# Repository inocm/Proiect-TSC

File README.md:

# Proiect InkTime: Smartwatch nRF52840

## 1. Diagrama Bloc

Diagrama de mai jos ilustreaza interconexiunile dintre unitatea centrala (MCU) si perifericele sistemului.

## 2. Descriere Hardware

Ceasul este construit in jurul lui **nRF52840**, ales pentru eficienta energetica ridicata si radio Bluetooth integrat. Principiul fundamental al proiectului: curentul este consumat exclusiv atunci cand este strict necesar.

### 2.1. Unitatea Centrala (MCU)
* **nRF52840:** Microcontroller cu suport nativ pentru Bluetooth 5.0 si USB. Dispune de doua cristale de cuart pentru precizie maxima in masurarea timpului — unul de 32 MHz (HFXO) pentru operatiunile de baza si radio, si unul de 32.768 kHz (LFXO) pentru RTC si modurile de sleep.
* **Antena:** Semnalul radio este directionat catre o antena ceramica **2450AT18B100E** de 2.4 GHz. Pentru a maximiza performanta RF, planul de cupru de sub antena a fost decupat (zona de „keep-out").

### 2.2. Alimentare si Baterie
* **Incarcator (BQ25180YBGR):** Gestioneaza incarcarea bateriei LiPo printr-o conexiune USB-C, inclusiv controlul power path-ului. Comunicarea se face prin **I2C**, permitand monitorizarea starii de incarcare.
* **Fuel Gauge (MAX17048G+T10):** Monitorizeaza cu precizie nivelul de incarcare al bateriei, cu o eroare sub 1%. Poate notifica MCU-ul printr-un pin de alerta atunci cand tensiunea coboara sub un prag configurat.
* **Regulator (RT6160AWSC):** Convertor buck-boost care livreaza un rail stabil de **3.3V** intregului sistem, indiferent de variatiile tensiunii bateriei.
* **Protectie ESD (USBLC6-2SC6Y):** Amplasata direct langa mufa USB-C, atenueaza descarcarile electrostatice pentru a proteja liniile de date ale interfetei.

### 2.3. Display si Feedback Haptic
* **Display E-Paper:** Avantajul principal al acestei tehnologii este ca nu consuma curent decat in momentul actualizarii imaginii. In stare statica, consumul este practic zero.
* **Circuit de driver E-Paper:** Display-ul necesita tensiuni ridicate pentru a misca cerneala electronica. Un circuit dedicat (bobina, diode Schottky si condensatori de 50V) genereaza tensiunile VGH si VGL necesare. Un P-FET (**SI2301CDS**) comanda complet alimentarea display-ului in standby.
* **Driver Haptic (DRV2605LDGSR):** Controleaza motorul ERM (LCM1027B3605F) cu o biblioteca interna de efecte de vibratie, oferind un feedback mai fin si mai variat fata de o simpla comutare cu tranzistor.

### 2.4. Senzori si Butoane
* **Accelerometru (BMA421):** Utilizat pentru numararea pasilor si detectarea miscarii. Conectat pe magistrala **I2C**, pinii sai de intrerupere (INT1, INT2) pot trezi MCU-ul din sleep la ridicarea incheieturii mainii.
* **Butoane (x3 EVP-AKE31A):** Trei butoane tactile SMD pentru navigarea interfetei (sus, jos, enter). Fiecare buton este echipat cu filtre hardware RC pentru eliminarea problemelor de debounce.

## 3. Asociere Pini nRF52840

| Grupa de pini | Pini folositi | Componenta | Justificarea alegerii / Functia |
| :--- | :--- | :--- | :--- |
| **I2C (SDA/SCL)** | **P0.06 / P0.07** | BQ25180, MAX17048, BMA421, DRV2605 | Magistrala I2C comuna; pozitionati departe de zona antenei pentru a evita interferentele RF. Pull-up 10k pe fiecare linie. |
| **Display (SPI)** | **P0.02 (SCK), P0.03 (MOSI)** | Conector FPC E-Paper | Rutare scurta si directa catre conectorul FPC, minimizand lungimea traseelor de mare viteza. |
| **Display Control** | **P0.05 (CS), P0.15, P0.16, P0.17** | Conector FPC E-Paper | Semnale GPIO pentru DC, Reset, Busy. Pinul Busy actioneaza ca intrerupere hardware. |
| **Power Gate Display** | **P1.01** | P-FET SI2301CDS | Comanda tranzistorul de putere care opreste complet alimentarea display-ului in modul standby. |
| **Butoane** | **P0.13, P0.14 / P1.02** | SW1, SW2, SW3 | Buton Enter, Buton Sus (Port 0) si Buton Jos (Port 1). |
| **Alerte & Intreruperi** | **P1.00 – P1.08** | IMU (INT1/INT2), Alerta baterie | Utilizarea portului P1 pentru semnale lente si intreruperi, izolandu-le de magistralele de date rapide. Permite wake-up eficient. |
| **Haptic Enable** | **P0.12** | DRV2605LDGSR | Pin GPIO pentru pornirea/oprirea cipului haptic. |
| **Fuel Gauge Alert** | **P0.10** | MAX17048 | Notificare de la fuel gauge cand tensiunea bateriei scade sub pragul configurat. |
| **Charger Alert** | **P0.11** | BQ25180 | Semnal de alerta de la incarcator pentru potentiale probleme de alimentare. |
| **USB** | **VBUS, D+, D-** | Conector USB-C KH-TYPE-C-16P | Pini hardware dedicati ai PHY-ului intern nRF52840 pentru comunicatie USB nativa. CC1/CC2 cu pull-down 5.1k. |
| **Programare (SWD)** | **SWDIO, SWDCLK, SWO** | Conector Tag-Connect TC2030 | Pini dedicati din fabrica pentru interfata Serial Wire Debug si programare. |
| **Oscilator HF** | **XC1, XC2** | Cristal 32 MHz (2016) | Pini hardware dedicati (HFXO) pentru cristalul extern necesar functionarii MCU si a modulului radio. |
| **Oscilator LF** | **XL1, XL2** | Cristal 32.768 kHz (3215) | Pini hardware dedicati (LFXO) pentru RTC si functiile de Low-Power Sleep. |

## 4. BOM

### Componente Active

| Qty | Componenta | Designator | Cod JLCPCB | Datasheet |
| :--- | :--- | :--- | :--- | :--- |
| 1 | **nRF52840-QIAA-R** (MCU) | U1 | [C190794](https://jlcpcb.com/partdetail/Nordic_Semicon-NRF52840_QIAA_R/C190794) | [Datasheet](https://infocenter.nordicsemi.com/pdf/nRF52840_PS_v1.8.pdf) |
| 1 | **BQ25180YBGR** (Charger) | IC1 | [C3682423](https://jlcpcb.com/partdetail/TexasInstruments-BQ25180YBGR/C3682423) | [Datasheet](https://www.ti.com/lit/ds/symlink/bq25180.pdf) |
| 1 | **RT6160AWSC** (DC/DC) | IC9 | [C7065276](https://jlcpcb.com/partdetail/Richtek_Tech-RT6160AWSC/C7065276) | [Datasheet](https://www.richtek.com/assets/product_file/RT6160A/DS6160A-05.pdf) |
| 1 | **MAX17048G+T10** (Fuel Gauge) | U3 | [C2682616](https://jlcpcb.com/partdetail/AnalogDevices-MAX17048G_T10/C2682616) | [Datasheet](https://www.analog.com/media/en/technical-documentation/data-sheets/MAX17048-MAX17049.pdf) |
| 1 | **BMA421** (Accelerometru) | IC3 | [C5242966](https://jlcpcb.com/partdetail/Bosch_Sensortec-BMA421/C5242966) | [Datasheet](https://www.bosch-sensortec.com/media/boschsensortec/downloads/datasheets/bst-bma421-ds004.pdf) |
| 1 | **DRV2605LDGSR** (Haptic) | IC4 | [C527464](https://jlcpcb.com/partdetail/TexasInstruments-DRV2605LDGSR/C527464) | [Datasheet](https://www.ti.com/lit/ds/symlink/drv2605l.pdf) |
| 1 | **SI2301CDS** (P-FET) | Q1 | [C10487](https://jlcpcb.com/partdetail/Changjiang_Electronics_Tech_CJ-SI2301CDS/C10487) | [Datasheet](https://www.vishay.com/docs/68749/si2301cds.pdf) |
| 1 | **USBLC6-2SC6Y** (ESD) | D3 | [C7519](https://jlcpcb.com/partdetail/Stmicroelectronics-USBLC6_2SC6Y/C7519) | [Datasheet](https://www.st.com/resource/en/datasheet/usblc6-2.pdf) |

### Conectori & Componente Electromecanice

| Qty | Componenta | Designator | Cod JLCPCB | Datasheet |
| :--- | :--- | :--- | :--- | :--- |
| 1 | **Molex 503480-2400** (FPC 24-pin) | J1 | [C2857160](https://jlcpcb.com/partdetail/Molex-5034802400/C2857160) | [Datasheet](https://www.molex.com/en-us/products/part-detail/5034802400) |
| 1 | **KH-TYPE-C-16P** (USB-C) | J4 | [C2765186](https://jlcpcb.com/partdetail/Kinghelm-KH_TYPE_C_16P/C2765186) | [Datasheet](https://datasheet.lcsc.com/lcsc/2012121836_Kinghelm-KH-TYPE-C-16P_C2765186.pdf) |
| 3 | **EVP-AKE31A** (Butoane) | SW1-SW3 | [C2845028](https://jlcpcb.com/partdetail/Panasonic-EVP_AKE31A/C2845028) | [Datasheet](https://industrial.panasonic.com/cdbs/www-data/pdf/ATV0000/ATV0000CE3.pdf) |
| 1 | **TC2030-IDC** (SWD Header) | J_SWD | — | [Datasheet](https://www.tag-connect.com/product/tc2030-idc) |
| 1 | **2450AT18B100E** (Antena 2.4GHz) | ANT1 | [C5179427](https://jlcpcb.com/partdetail/Johanson_Technology-2450AT18B100E/C5179427) | [Datasheet](https://www.johansontechnology.com/datasheets/2450AT18B100/2450AT18B100.pdf) |

### Componente Pasive (selectie)

| Componenta | Valoare | Pachet | Cantitate | Rol |
| :--- | :--- | :--- | :--- | :--- |
| Condensatori EPD | 1uF / 50V | 0402 | 9 | Driver circuit e-paper (VGH/VGL) |
| Condensatori decuplare | 100nF | 0201 | 5 | Decuplare MCU si periferice |
| Condensatori incarcare cristal | 12pF | 0201 | 4 | Load capacitors 32MHz + 32.768kHz |
| Condensatori bulk MCU | 4.7uF | 0402 | 4 | Stabilizare rail 3V3 MCU |
| Condensatori BQ25180 | 1uF | 0402 | 3 | CIN / CSYS / CBAT charger |
| Condensatori RT6160 | 22uF | 0402 | 2 | Intrare convertor buck-boost |
| Condensator USB | 4.7uF | 0402 | 1 | DECUSB nRF52840 |
| Rezistori I2C pull-up | 10k | 0201 | 2 | Pull-up SDA / SCL |
| Rezistori USB CC | 5.1k | 0201 | 2 | Pull-down CC1 / CC2 USB-C |
| Bobina DC/DC nRF | 10uH | 0402 | 1 | Inductor REG1 intern nRF52840 |
| Bobina RT6160 | 0.47uH | 2012 | 1 | Etaj de putere buck-boost |
| Cristal HF | 32 MHz | 2016 | 1 | HFXO — MCU + radio |
| Cristal LF | 32.768 kHz | 3215 | 1 | LFXO — RTC + sleep |

### Componente Asamblate Manual

| Componenta | Descriere | Datasheet |
| :--- | :--- | :--- |
| Display E-Paper | Panou 1.54" 200×200 px, conectat prin FPC 24-pin | [Datasheet](https://www.tme.eu/Document/0ca57a8ffbcd57b5bca53252eb9d6ec3/WSH-12561.pdf) |
| Baterie LiPo | 3.7V / 250mAh, conectata prin fire la test pad-uri | [Datasheet](https://www.tme.eu/Document/b9e12bf26ad0ba929a22ab5d58f022cd/AKY0106.pdf) |
| Motor ERM | Motor vibratii LCM1027B3605F, lipit direct prin fire | [Datasheet](https://www.mouser.com/pdfDocs/ProductOverview_DFRobot-FIT0774.pdf) |
| Carcasa | Prototip imprimat 3D (FDM / SLS) | [Soon™](https://www.youtube.com/watch?v=xm3YgoEiEDc) |

## 5. Decizii de Design

### 5.1. Amplasarea Componentelor pe PCB

Au fost luate urmatoarele decizii strategice pentru a optimiza spatiul, performanta si integritatea semnalului:

* **PCB pe 4 straturi:** Stackup-ul folosit: Top (semnal), GND plane (layer 2), 3V3 plane (layer 3), Bottom (semnal). Aceasta structura ofera o referinta de masa solida pentru traseele de semnal si reduce EMI-ul intern.

* **Planuri de Masa (GND Pours) pe straturi Top si Bottom:** Poligoanele de GND sunt cusute cu via-uri (stitching vias) si servesc trei scopuri:
    1. **Ecranare EMI:** Reduce cuplajul electromagnetic intre traseele de semnal.
    2. **Disipare Termica:** Ajuta la evacuarea caldurii de la convertorul DC/DC si circuitul de incarcare.
    3. **Referinta RF:** Furnizeaza un plan de masa de calitate pentru performanta optima a antenei Bluetooth.

* **Zona RF Keep-out (Antena):** Antena ceramica de 2.4 GHz este pozitionata la extremitatea placii, cu toate straturile de cupru decupate pe sub ea. Grupul de alimentare (charger, fuel gauge, regulator) este plasat la distanta maxima pentru a evita cuplajul cu traseele RF sensibile.

* **Gruparea Circuitului E-Paper:** Componentele aferente display-ului (bobina, diodele si condensatorii de 50V pentru VGH/VGL) sunt concentrate compact imediat langa conectorul FPC. Traseele de inalta tensiune ramane astfel scurte si departe de liniile sensibile ale MCU.

* **Via-in-pad:** Pentru componentele cu footprint mic (WLCSP, DFN), a fost folosita tehnica via-in-pad. Aceasta genereaza cateva avertismente DRC, dar a fost singura solutie viabila pentru rutarea in spatiul disponibil.

* **Conectorul FPC (Display):** Conectorul flex al display-ului a fost curbat in modelul 3D pentru a se potrivi corect in pozitia de asamblare, folosind comanda bend pentru metal sheets din Fusion 360.

### 5.2. Erori Known si Justificari

#### Erori ERC (Electrical Rule Check)
* **Conflicte de alimentare (U1, U3):** Softul semnaleaza erori deoarece mai multi pini `VDD` se conecteaza la aceeasi retea (`3V3` sau `VBAT`). Conexiunile sunt corecte conform datasheet-urilor; eroarea este un fals pozitiv cauzat de restrictiile prea stricte ale tool-ului in legatura cu tipurile de „Power Source".
* **Pinii de decuplare (DEC1, DEC4):** Similar cu cazul anterior, pinii speciali de decuplare ai nRF52840 sunt conectati corect conform recomandarilor producatorului, insa nu sunt recunoscuti ca noduri clasice de alimentare de catre ERC.
* **Componente fara valoare (SJ1):** Jumper-ul SJ1 este un simplu Solder Jumper pentru configurare hardware — un contact de lipit fara valoare numerica, ceea ce este comportamentul asteptat.
* **"Only one pin on net" (SDA/SCL):** Indica trasee lasate fara conexiune la un capat; nu reprezinta o eroare functionala.

#### Erori DRC (Design Rule Check)
Deoarece acest PCB este un *Proof of Concept* si nu este destinat productiei imediate, unele compromisuri de DRC au fost acceptate constient:
* **Board Outline Clearance (8 erori):** Conectorul USB-C si butoanele sunt apropiate de marginea placii prin constrangeri de form factor, declansand automat aceste avertismente.
* **Polygon Overlap (clearance pad-uri):** Placa foloseste componente minuscule (0201/0402) si este extrem de aglomerata. Planul de masa a fost fortat sa acopere cat mai mult spatiu pentru o disipare termica optima, in detrimentul unui raport DRC perfect.

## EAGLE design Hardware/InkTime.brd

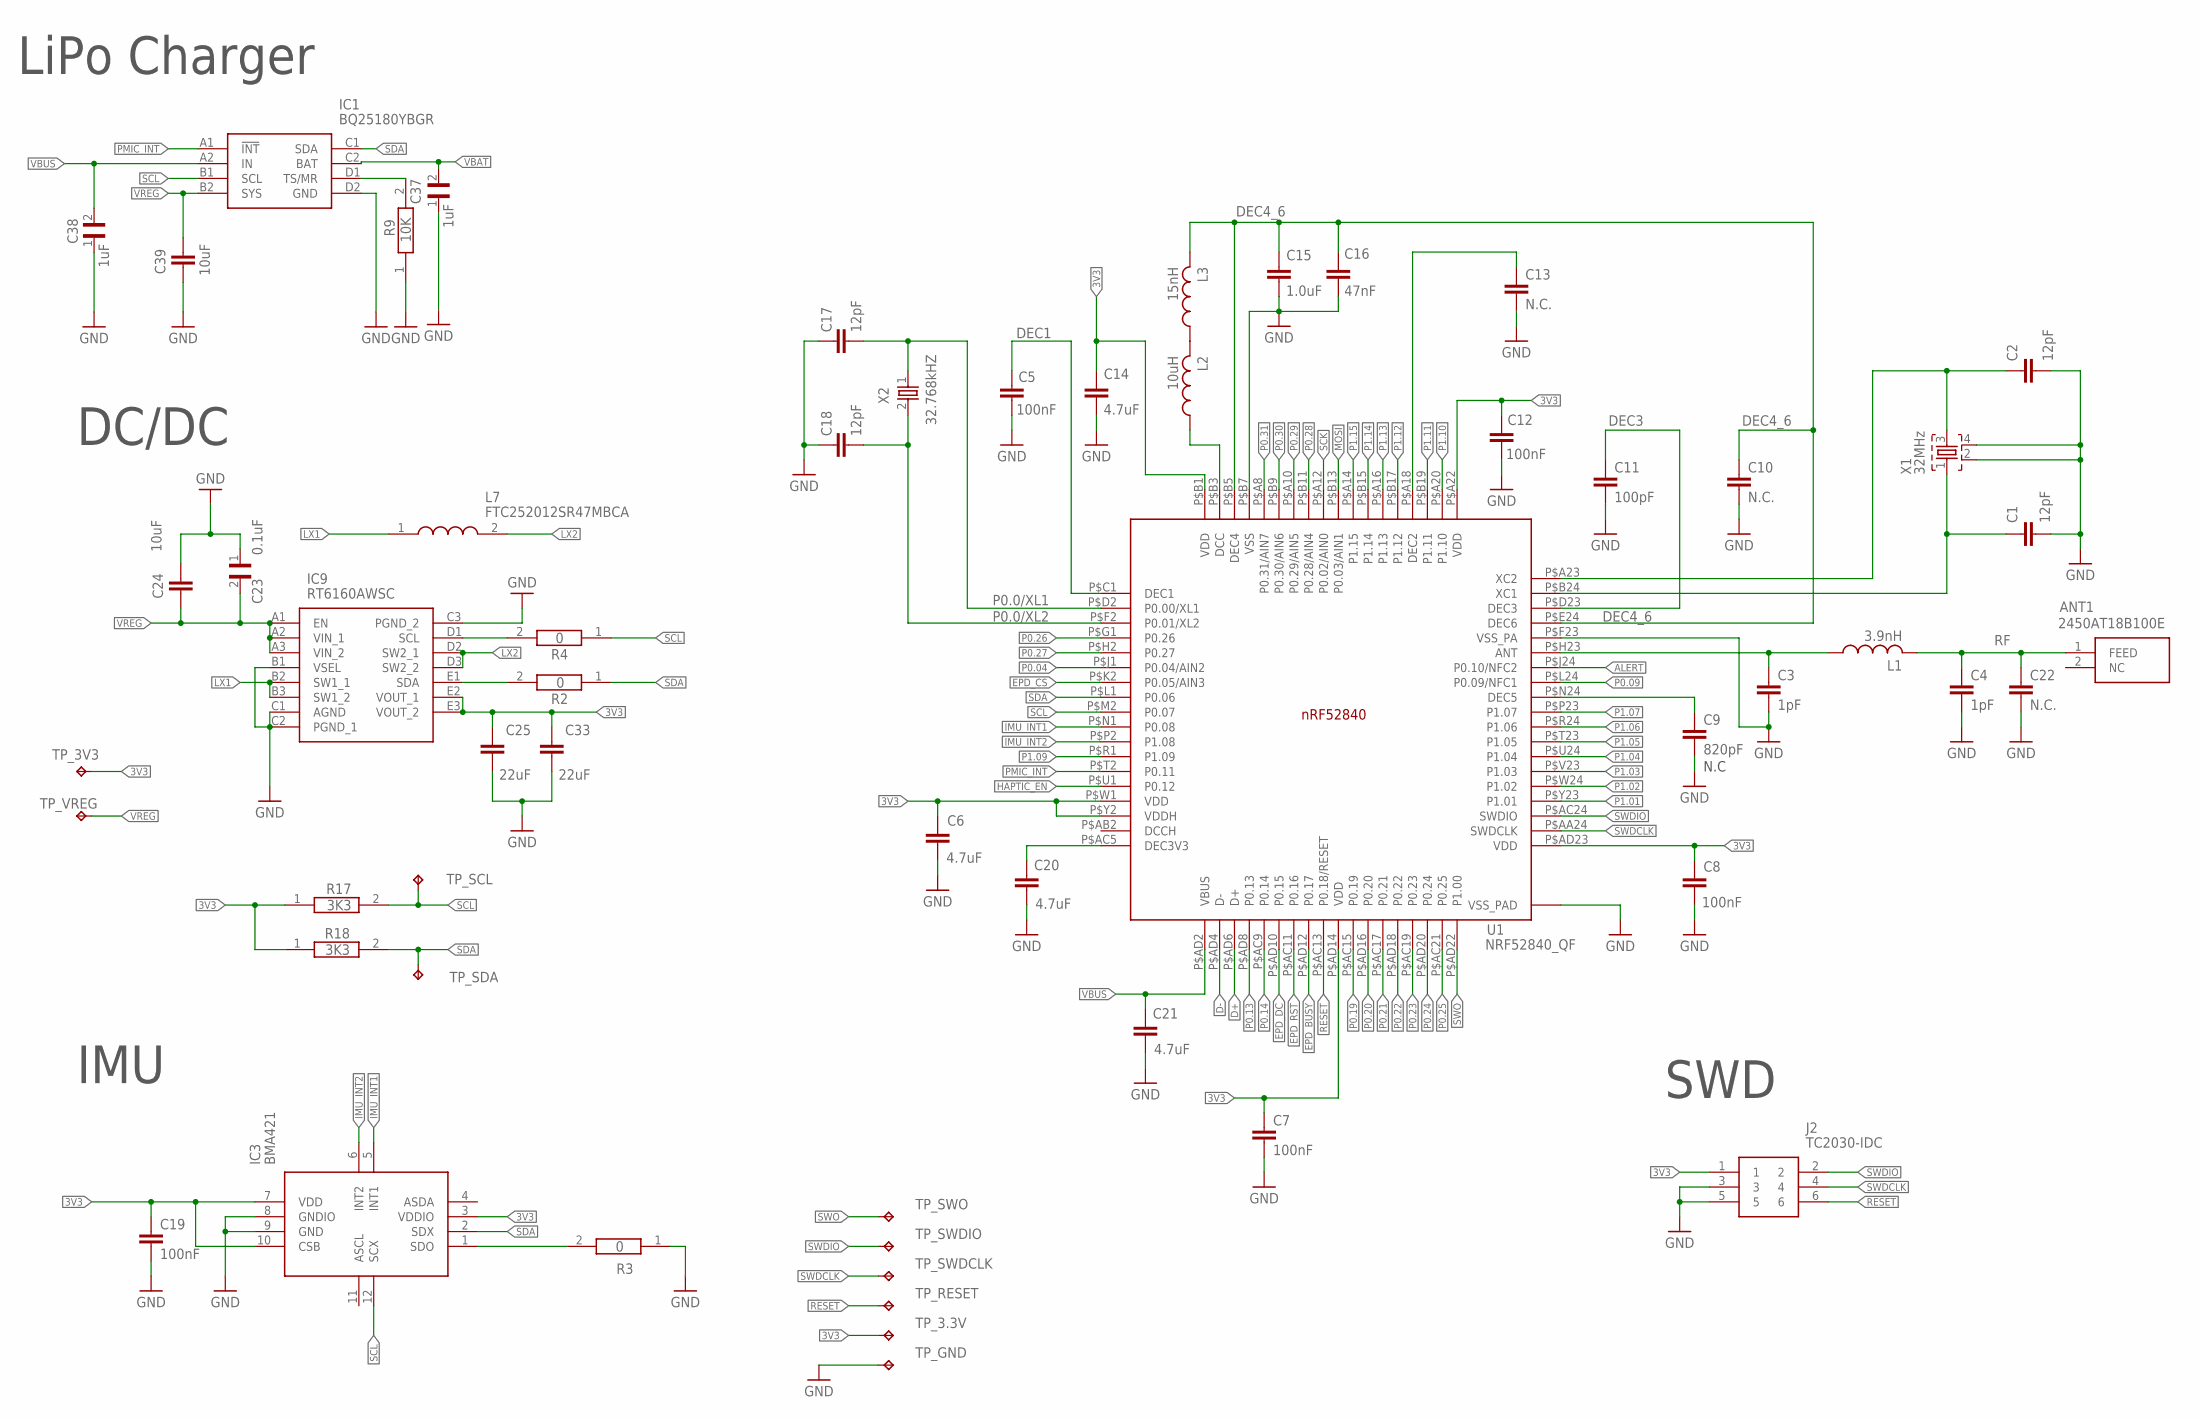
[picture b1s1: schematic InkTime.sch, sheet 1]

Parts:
ANT1: 2450AT18B100E; 2450AT18B100E_ANTC3216X140N
C1, C2, C17, C18: 12pF; NORDIC_NRF_3_RESC0201_L
C3, C4: 1pF; NORDIC_NRF_3_RESC0201_L
C5: 100nF; PERFECT_0402_0402
C6, C14, C20, C21: 4.7uF; PERFECT_0402_0402
C7, C8, C12, C19: 100nF; NORDIC_NRF_3_RESC0201_L
C9: 820pF; NORDIC_NRF_3_RESC0201_L
C10, C13, C22: N.C.; NORDIC_NRF_3_RESC0201_L
C11: 100pF; NORDIC_NRF_3_RESC0201_L
C15: 1.0uF; PERFECT_0402_0402
C16: 47nF; NORDIC_NRF_3_RESC0201_L
C23: 0.1uF; GRM011R60J152KE01L_1_0201
C24, C39: 10uF; PERFECT_0402_0402
C25, C33: 22uF; PERFECT_0402_0402
C37, C38: 1uF; GRM011R60J152KE01L_1_0201
IC1: BQ25180YBGR; BQ25180YBGR_BGA8C40P2X4_100X155X50
IC3: BMA421; BMA423_BMA423
IC9: RT6160AWSC; RT6160AWSC_BGA15C40P3X5_140X230X60
J2: TC2030-IDC; TC2030-IDC_TC2030IDC
L1: 3.9nH; NORDIC_NRF_2_RESC0402_L
L2: 10uH; NORDIC_NRF_2_RESC0402_L
L3: 15nH; NORDIC_NRF_2_RESC0402_L
L7: FTC252012SR47MBCA; MLP2016SR47MT0S1_INDC2016X100N
R2, R3, R4: 0; ERA-1AEB3401C_0201
R9: 10K; ERA-1AEB3401C_0201
R17, R18: 3K3; ERA-1AEB3401C_0201
TP_3.3V, TP_3V3: HECTOR_WATCH_1_TPTP20R; HECTOR_WATCH_1_TP20R
TP_GND: HECTOR_WATCH_1_TPTP20R; HECTOR_WATCH_1_TP20R
TP_RESET: HECTOR_WATCH_1_TPTP20R; HECTOR_WATCH_1_TP20R
TP_SCL: HECTOR_WATCH_1_TPTP20R; HECTOR_WATCH_1_TP20R
TP_SDA: HECTOR_WATCH_1_TPTP20R; HECTOR_WATCH_1_TP20R
TP_SWDCLK: HECTOR_WATCH_1_TPTP20R; HECTOR_WATCH_1_TP20R
TP_SWDIO: HECTOR_WATCH_1_TPTP20R; HECTOR_WATCH_1_TP20R
TP_SWO: HECTOR_WATCH_1_TPTP20R; HECTOR_WATCH_1_TP20R
TP_VREG: HECTOR_WATCH_1_TPTP20R; HECTOR_WATCH_1_TP20R
U1: NRF52840_QF; NORDIC_NRF_4_AQFN50P700X700X85_HS-74N
X1: 32MHz; NORDIC_NRF_BT-XTAL_2016_N
X2: 32.768kHZ; NORDIC_NRF_1_XTAL_3215_N

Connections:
3V3: C6.1, C7.1, C8.1, C12.1, C14.1, C19.1, C25.1, C33.1, IC3.3 (VDDIO), IC3.7 (VDD), IC3.10 (CSB), IC9.E2 (VOUT_1), IC9.E3 (VOUT_2), J2.1, R17.1, R18.1, TP_3.3V.TP, TP_3V3.TP, U1.P$A22 (VDD), U1.P$AD14 (VDD), U1.P$AD23 (VDD), U1.P$B1 (VDD), U1.P$W1 (VDD), U1.P$Y2 (VDDH); also elsewhere on the board
ALERT: U1.P$J24 (P0.10/NFC2); also elsewhere on the board
D+: U1.P$AD6 (D+); also elsewhere on the board
D-: U1.P$AD4 (D-); also elsewhere on the board
DEC1: C5.1, U1.P$C1 (DEC1)
DEC3: C11.1, U1.P$D23 (DEC3)
DEC4_6: C10.1, C15.1, C16.1, L3.2, U1.P$B5 (DEC4), U1.P$E24 (DEC6)
EPD_BUSY: U1.P$AD12 (P0.17); also elsewhere on the board
EPD_CS: U1.P$K2 (P0.05/AIN3); also elsewhere on the board
EPD_DC: U1.P$AD10 (P0.15); also elsewhere on the board
EPD_RST: U1.P$AC11 (P0.16); also elsewhere on the board
GND: C1.1, C2.1, C3.2, C4.2, C5.2, C6.2, C7.2, C8.2, C9.2, C10.2, C11.2, C12.2, C13.2, C14.2, C15.2, C16.2, C17.1, C18.1, C19.2, C20.2, C21.2, C22.2, C23.1, C24.1, C25.2, C33.2, C37.1, C38.1, C39.2, IC1.D2 (GND), IC3.8 (GNDIO), IC3.9 (GND), IC9.B1 (VSEL), IC9.C1 (AGND), IC9.C2 (PGND_1), IC9.C3 (PGND_2), J2.3, J2.5, R3.1, R9.1, TP_GND.TP, U1.P$74 (VSS_PAD), U1.P$75 (VSS_PAD), U1.P$76 (VSS_PAD), U1.P$77 (VSS_PAD), U1.P$78 (VSS_PAD), U1.P$79 (VSS_PAD), U1.P$80 (VSS_PAD), U1.P$81 (VSS_PAD), U1.P$82 (VSS_PAD), U1.P$83 (VSS_PAD), U1.P$84 (VSS_PAD), U1.P$85 (VSS_PAD), U1.P$86 (VSS_PAD), U1.P$87 (VSS_PAD), U1.P$88 (VSS_PAD), U1.P$89 (VSS_PAD), U1.P$90 (VSS_PAD), U1.P$B7 (VSS), U1.P$F23 (VSS_PA), X1.2, X1.4; also elsewhere on the board
HAPTIC_EN: U1.P$U1 (P0.12); also elsewhere on the board
IMU_INT1: IC3.5 (INT1), U1.P$N1 (P0.08)
IMU_INT2: IC3.6 (INT2), U1.P$P2 (P1.08)
LX1: IC9.B2 (SW1_1), IC9.B3 (SW1_2), L7.1
LX2: IC9.D2 (SW2_1), IC9.D3 (SW2_2), L7.2
MOSI: U1.P$B13 (P0.03/AIN1); also elsewhere on the board
unnamed: IC1.D1 (TS/MR), R9.2
unnamed: IC9.D1 (SCL), R4.2
unnamed: IC9.E1 (SDA), R2.2
unnamed: C9.1, U1.P$N24 (DEC5)
unnamed: C3.1, L1.1, U1.P$H23 (ANT)
unnamed: IC3.1 (SDO), R3.2
unnamed: L2.1, U1.P$B3 (DCC)
unnamed: L2.2, L3.1
unnamed: C1.2, U1.P$B24 (XC1), X1.1
unnamed: C13.1, U1.P$A18 (DEC2)
unnamed: C2.2, U1.P$A23 (XC2), X1.3
P0.0/XL1: C17.2, U1.P$D2 (P0.00/XL1), X2.1
P0.0/XL2: C18.2, U1.P$F2 (P0.01/XL2), X2.2
P0.04: U1.P$J1 (P0.04/AIN2)
P0.09: U1.P$L24 (P0.09/NFC1)
P0.13: U1.P$AD8 (P0.13); also elsewhere on the board
P0.14: U1.P$AC9 (P0.14); also elsewhere on the board
P0.19: U1.P$AC15 (P0.19)
P0.20: U1.P$AD16 (P0.20)
P0.21: U1.P$AC17 (P0.21)
P0.22: U1.P$AD18 (P0.22)
P0.23: U1.P$AC19 (P0.23)
P0.24: U1.P$AD20 (P0.24)
P0.25: U1.P$AC21 (P0.25)
P0.26: U1.P$G1 (P0.26)
P0.27: U1.P$H2 (P0.27)
P0.28: U1.P$B11 (P0.28/AIN4)
P0.29: U1.P$A10 (P0.29/AIN5)
P0.30: U1.P$B9 (P0.30/AIN6)
P0.31: U1.P$A8 (P0.31/AIN7)
P1.01: U1.P$Y23 (P1.01); also elsewhere on the board
P1.02: U1.P$W24 (P1.02); also elsewhere on the board
P1.03: U1.P$V23 (P1.03)
P1.04: U1.P$U24 (P1.04)
P1.05: U1.P$T23 (P1.05)
P1.06: U1.P$R24 (P1.06)
P1.07: U1.P$P23 (P1.07)
P1.09: U1.P$R1 (P1.09)
P1.10: U1.P$A20 (P1.10)
P1.11: U1.P$B19 (P1.11)
P1.12: U1.P$B17 (P1.12)
P1.13: U1.P$A16 (P1.13)
P1.14: U1.P$B15 (P1.14)
P1.15: U1.P$A14 (P1.15)
PMIC_INT: IC1.A1 (!INT), U1.P$T2 (P0.11)
RESET: J2.6, TP_RESET.TP, U1.P$AC13 (P0.18/RESET); also elsewhere on the board
RF: ANT1.1 (FEED), C4.1, C22.1, L1.2
SCK: U1.P$A12 (P0.02/AIN0); also elsewhere on the board
SCL: IC1.B1 (SCL), IC3.12 (SCX), R4.1, R17.2, TP_SCL.TP, U1.P$M2 (P0.07); also elsewhere on the board
SDA: IC1.C1 (SDA), IC3.2 (SDX), R2.1, R18.2, TP_SDA.TP, U1.P$L1 (P0.06); also elsewhere on the board
SWDCLK: J2.4, TP_SWDCLK.TP, U1.P$AA24 (SWDCLK)
SWDIO: J2.2, TP_SWDIO.TP, U1.P$AC24 (SWDIO)
SWO: TP_SWO.TP, U1.P$AD22 (P1.00)
VBAT: C37.2, IC1.C2 (BAT); also elsewhere on the board
VBUS: C21.1, C38.2, IC1.A2 (IN), U1.P$AD2 (VBUS); also elsewhere on the board
VBUS/2.6D1: C20.1, U1.P$AC5 (DEC3V3)
VREG: C23.2, C24.2, C39.1, IC1.B2 (SYS), IC9.A1 (EN), IC9.A2 (VIN_1), IC9.A3 (VIN_2), TP_VREG.TP

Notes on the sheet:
LiPo Charger
IMU
DC/DC
SWD
N.C

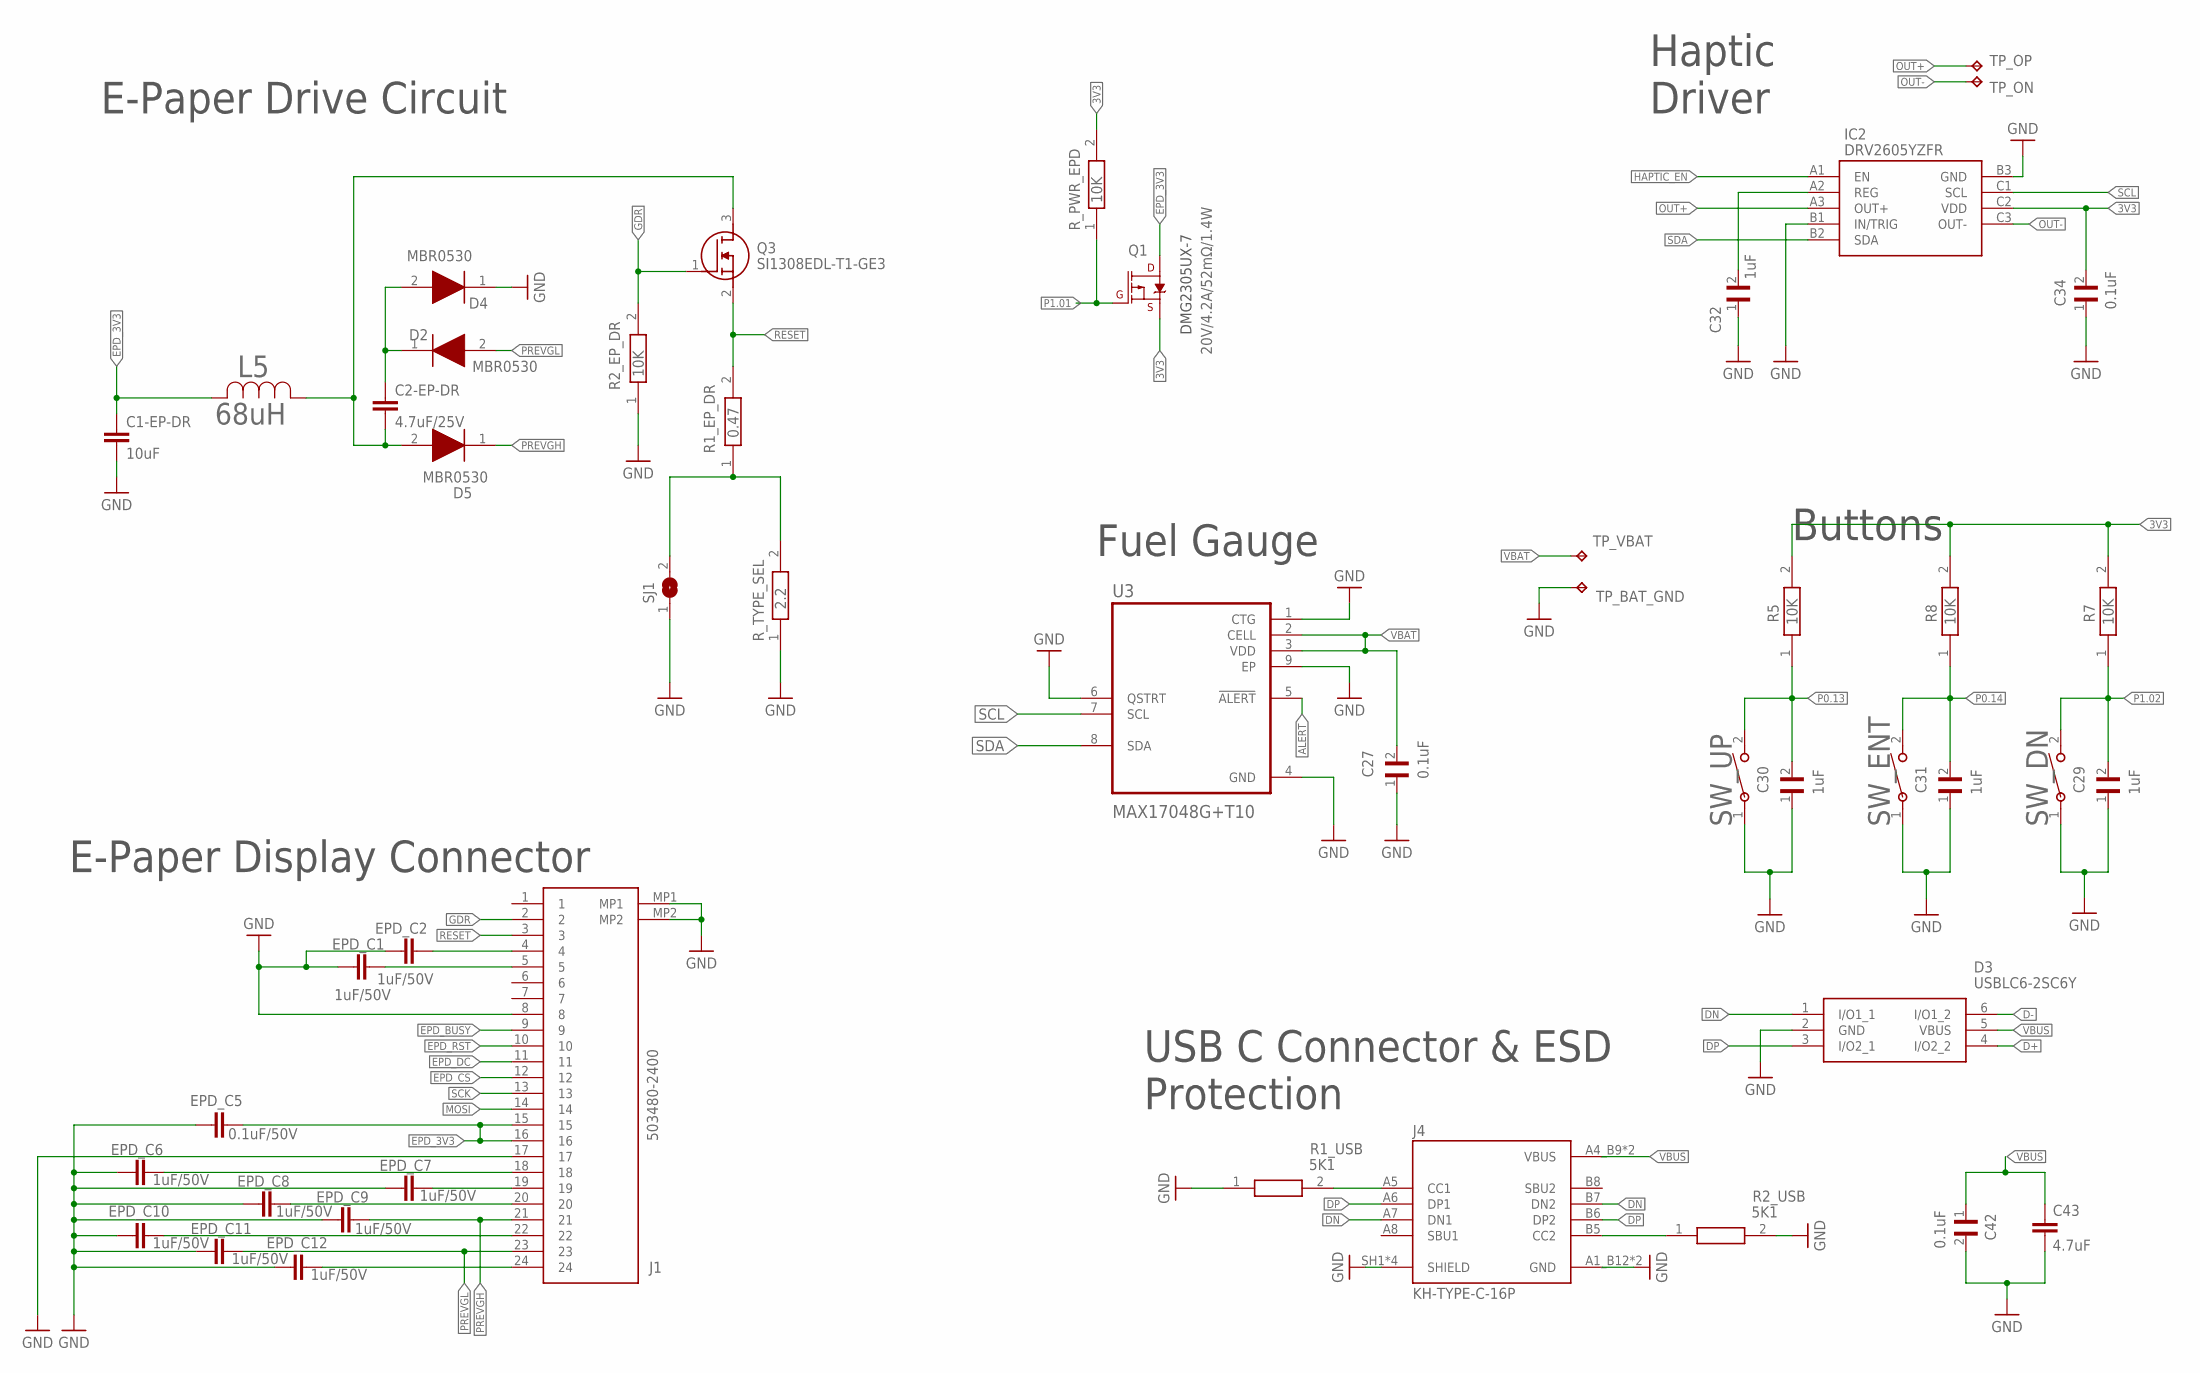
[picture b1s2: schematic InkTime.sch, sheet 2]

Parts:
C1-EP-DR: 10uF; PERFECT_0402_0402
C2-EP-DR: 4.7uF/25V; PERFECT_0402_0402
C27, C34, C42: 0.1uF; GRM011R60J152KE01L_1_0201
C29, C30, C31, C32: 1uF; GRM011R60J152KE01L_1_0201
C43: 4.7uF; PERFECT_0402_0402
D2, D4, D5: MBR0530; ESP32_C6_LIBRARY_5_SOD3716X135N
D3: USBLC6-2SC6Y; ESP32_C6_LIBRARY_3_SOT95P280X145-6N
EPD_C1, EPD_C2, EPD_C6, EPD_C7, EPD_C8, EPD_C9, EPD_C10, EPD_C11, EPD_C12: 1uF/50V; PERFECT_0402_0402
EPD_C5: 0.1uF/50V; NORDIC_NRF_3_RESC0201_L
IC2: DRV2605YZFR; DRV2605YZFR_BGA9C50P3X3_144X144X62
J1: 503480-2400; 503480-2400_5034802400
J4: KH-TYPE-C-16P; KH-TYPE-C-16P_KINGHELM_KH-TYPE-C-16P
L5: 68uH; ESP32_C6_LIBRARY_2_IND_4828-WE-TPC_WRE
Q1: 20V/4.2A/52mΩ/1.4W; ESP32_C6_LIBRARY_4_ESP32_C6_LIBRARY_4_ESP32_C6_LIBRARY_4_ES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
Q3: SI1308EDL-T1-GE3; ESP32_C6_LIBRARY_6_SOT65P210X110-3N
R1_EP_DR: 0.47; ERA-1AEB3401C_0201
R1_USB, R2_USB: 5K1; ERA-1AEB3401C_0201
R2_EP_DR, R5, R7, R8: 10K; ERA-1AEB3401C_0201
R_PWR_EPD: 10K; ERA-1AEB3401C_0201
R_TYPE_SEL: 2.2; ERA-1AEB3401C_0201
SJ1: ESP32_C6_LIBRARY_7_JUMPER_SJ
SW_DN: 2025-10-22_07-23-44_LIBRARY_EVP-AKE31ASW_EVP-AKE3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; 2025-10-22_07-23-44_LIBRARY_SW_EVP-AKE31A_PAN
SW_ENT: 2025-10-22_07-23-44_LIBRARY_EVP-AKE31ASW_EVP-AKE3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; 2025-10-22_07-23-44_LIBRARY_SW_EVP-AKE31A_PAN
SW_UP: 2025-10-22_07-23-44_LIBRARY_EVP-AKE31ASW_EVP-AKE3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; 2025-10-22_07-23-44_LIBRARY_SW_EVP-AKE31A_PAN
TP_BAT_GND: HECTOR_WATCH_1_TPTP20R; HECTOR_WATCH_1_TP20R
TP_ON: HECTOR_WATCH_1_TPTP20R; HECTOR_WATCH_1_TP20R
TP_OP: HECTOR_WATCH_1_TPTP20R; HECTOR_WATCH_1_TP20R
TP_VBAT: HECTOR_WATCH_1_TPTP20R; HECTOR_WATCH_1_TP20R
U3: MAX17048G+T10; ESP32_C6_LIBRARY_SON50P200X200X80-9N

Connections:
3V3: C34.2, IC2.C2 (VDD), Q1.2 (S), R5.2, R7.2, R8.2, R_PWR_EPD.2; also elsewhere on the board
ALERT: U3.5 (!ALERT); also elsewhere on the board
D+: D3.4 (I/O2_2); also elsewhere on the board
D-: D3.6 (I/O1_2); also elsewhere on the board
DN: D3.1 (I/O1_1), J4.A7 (DN1), J4.B7 (DN2)
DP: D3.3 (I/O2_1), J4.A6 (DP1), J4.B6 (DP2)
EPD_3V1: C2-EP-DR.1, D2.1 (K), D4.2 (A)
EPD_3V3: C1-EP-DR.1, EPD_C5.2, J1.15, J1.16, L5.2, Q1.3 (D)
EPD_BUSY: J1.9; also elsewhere on the board
EPD_CS: J1.12; also elsewhere on the board
EPD_DC: J1.11; also elsewhere on the board
EPD_RST: J1.10; also elsewhere on the board
GDR: J1.2, Q3.1 (G), R2_EP_DR.2
GND: C1-EP-DR.2, C27.1, C29.1, C30.1, C31.1, C32.1, C34.1, C42.2, C43.1, D3.2 (GND), D4.1 (K), EPD_C1.1, EPD_C2.1, EPD_C5.1, EPD_C6.1, EPD_C7.1, EPD_C8.1, EPD_C9.1, EPD_C10.1, EPD_C11.1, EPD_C12.1, IC2.B1 (IN/TRIG), IC2.B3 (GND), J1.8, J1.17, J1.MP1, J1.MP2, J4.A1_B12 (GND), J4.A12_B1 (GND), J4.SH1 (SHIELD), J4.SH2 (SHIELD), J4.SH3 (SHIELD), J4.SH4 (SHIELD), R1_USB.1, R2_EP_DR.1, R2_USB.2, R_TYPE_SEL.1, SJ1.1, SW_DN.1, SW_ENT.1, SW_UP.1, TP_BAT_GND.TP, U3.1 (CTG), U3.4 (GND), U3.6 (QSTRT), U3.9 (EP); also elsewhere on the board
GND1: R1_EP_DR.1, R_TYPE_SEL.2, SJ1.2
GND2: J4.A5 (CC1), R1_USB.2
HAPTIC_EN: IC2.A1 (EN); also elsewhere on the board
MOSI: J1.14; also elsewhere on the board
unnamed: C2-EP-DR.2, D5.2 (A), L5.1, Q3.3 (D)
unnamed: EPD_C2.2, J1.4
unnamed: EPD_C1.2, J1.5
unnamed: EPD_C6.2, J1.18
unnamed: EPD_C7.2, J1.19
unnamed: J4.B5 (CC2), R2_USB.1
unnamed: EPD_C8.2, J1.20
unnamed: EPD_C10.2, J1.22
unnamed: EPD_C12.2, J1.24
OUT+: IC2.A3 (OUT+), TP_OP.TP
OUT-: IC2.C3 (OUT-), TP_ON.TP
P0.13: C30.2, R5.1, SW_UP.2; also elsewhere on the board
P0.13/1.5D1: C32.2, IC2.A2 (REG)
P0.14: C31.2, R8.1, SW_ENT.2; also elsewhere on the board
P1.01: Q1.1 (G), R_PWR_EPD.1; also elsewhere on the board
P1.02: C29.2, R7.1, SW_DN.2; also elsewhere on the board
PREVGH: D5.1 (K), EPD_C9.2, J1.21
PREVGL: D2.2 (A), EPD_C11.2, J1.23
RESET: J1.3, Q3.2 (S), R1_EP_DR.2; also elsewhere on the board
SCK: J1.13; also elsewhere on the board
SCL: IC2.C1 (SCL), U3.7 (SCL); also elsewhere on the board
SDA: IC2.B2 (SDA), U3.8 (SDA); also elsewhere on the board
VBAT: C27.2, TP_VBAT.TP, U3.2 (CELL), U3.3 (VDD); also elsewhere on the board
VBUS: C42.1, C43.2, D3.5 (VBUS), J4.A4_B9 (VBUS), J4.A9_B4 (VBUS); also elsewhere on the board

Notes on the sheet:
DMG2305UX-7
Fuel Gauge
E-Paper Drive Circuit
Haptic Driver
E-Paper Display Connector
USB C Connector & ESD Protection
Buttons

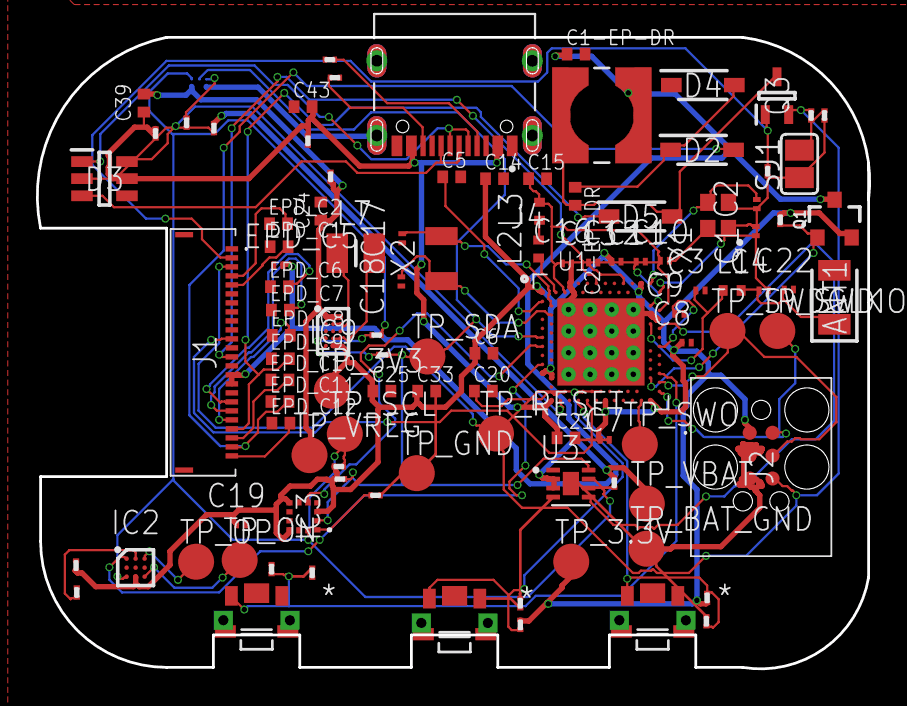
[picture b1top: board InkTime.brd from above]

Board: 4 copper layers, 46.2 x 35.1 mm, 105 parts (1 on the bottom side), 69 nets.

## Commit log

2026-04-10 Add Apache License 2.0
    Added Apache License 2.0 to the project.
2026-04-10 document
2026-04-10 README.md
2026-04-21 Revise README with comprehensive project details
    Updated the README to include detailed project information, hardware descriptions, pin assignments, BOM, design decisions, and known errors.
2026-04-21 Add image to hardware description section
2026-04-21 Add diagram to README for hardware description
    Added a diagram illustrating connections between the MCU and system peripherals.
2026-04-22 Fix image link for PCB 3D Top
    Updated image reference for PCB 3D Top in README.

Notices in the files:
parts and their libraries:
COPYRIGHT: Copyright (C) 2024 Ultra Librarian. All rights reserved.
COPYRIGHT: Copyright (C) 2025 Ultra Librarian. All rights reserved.
